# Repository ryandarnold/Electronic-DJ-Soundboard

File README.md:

# Electronic-DJ-Soundboard
The Electronic DJ Soundboard I designed in Eagle while serving as hardware lead on a 4-person team. I picked out the chips, designed the circuit, performed layout, soldered all components and tested and verified the board with a power supply and digital multimeter. 

I also coordinated with the embedded software lead on GPIO pin assignments, I/O functionality, communication protocol usage, and peripheral connections to support embedded firmware development.

<p align="center">
  
  <br>
  <em> The DJ circuit board outside its enclosure. I laser cut the enclosure and sanded it so it would fit together. </em>
</p>

<p align="center">
  
  <br>
  <em> The DJ circuit board from another angle. </em>
</p>

<p align="center">
  
  <br>
  <em> The main DJ circuit board.</em>
</p>

## Hardware: 

1. **TM4C123GH6PMI microcontroller launchpad** (as the main MCU for the project)
2. **Ceramic and Tantalum capacitors** (various purposes)
3. **ESP8266 Wifi module** (for saving user-made sound clips)
4. **TLV5618ACP DAC** (for outputting to the two speakers)
5. **MC34119 audio amplifier** (for amplifying the DAC output to the speakers)
6. **ULN2803a transistor array** (for powering the LED arrays)
7. **LM4041CILPR shunt voltage reference** (required for the TLV DAC)
8. **Resistors** (various purposes)
9. **Wire nuts** (for connecting the LEDs to the transistor array)
10. **LM2937 3.3 V regulator** (for powering different parts of the board)
11. **Testpoints** (for verifying that different parts of the board work)
12. **Blue, Red and Yellow LEDs** (to light the translucent buttons when pushed)
13. **MC7805ABTG 5V regulator** (for powering the LED array)
14. **8-ohm speakers** (for outputting user-made sounds)
15. **Audio jack** (so you can choose to use the built-in speakers or attach your own personal speaker for better sound quality)
16. **Pin headers**(to connect the launchpad to the board, and to have maximum flexibility in testing prototype)
17. **DC power connector** (to power the board)
18. **ST7735R LCD** (for displaying info to the user)
19. **Wood enclosure** (to store all electronics)
20. **Turn potentiometer** (for volume change)
21. **Slide potentiometer** (for tone change)

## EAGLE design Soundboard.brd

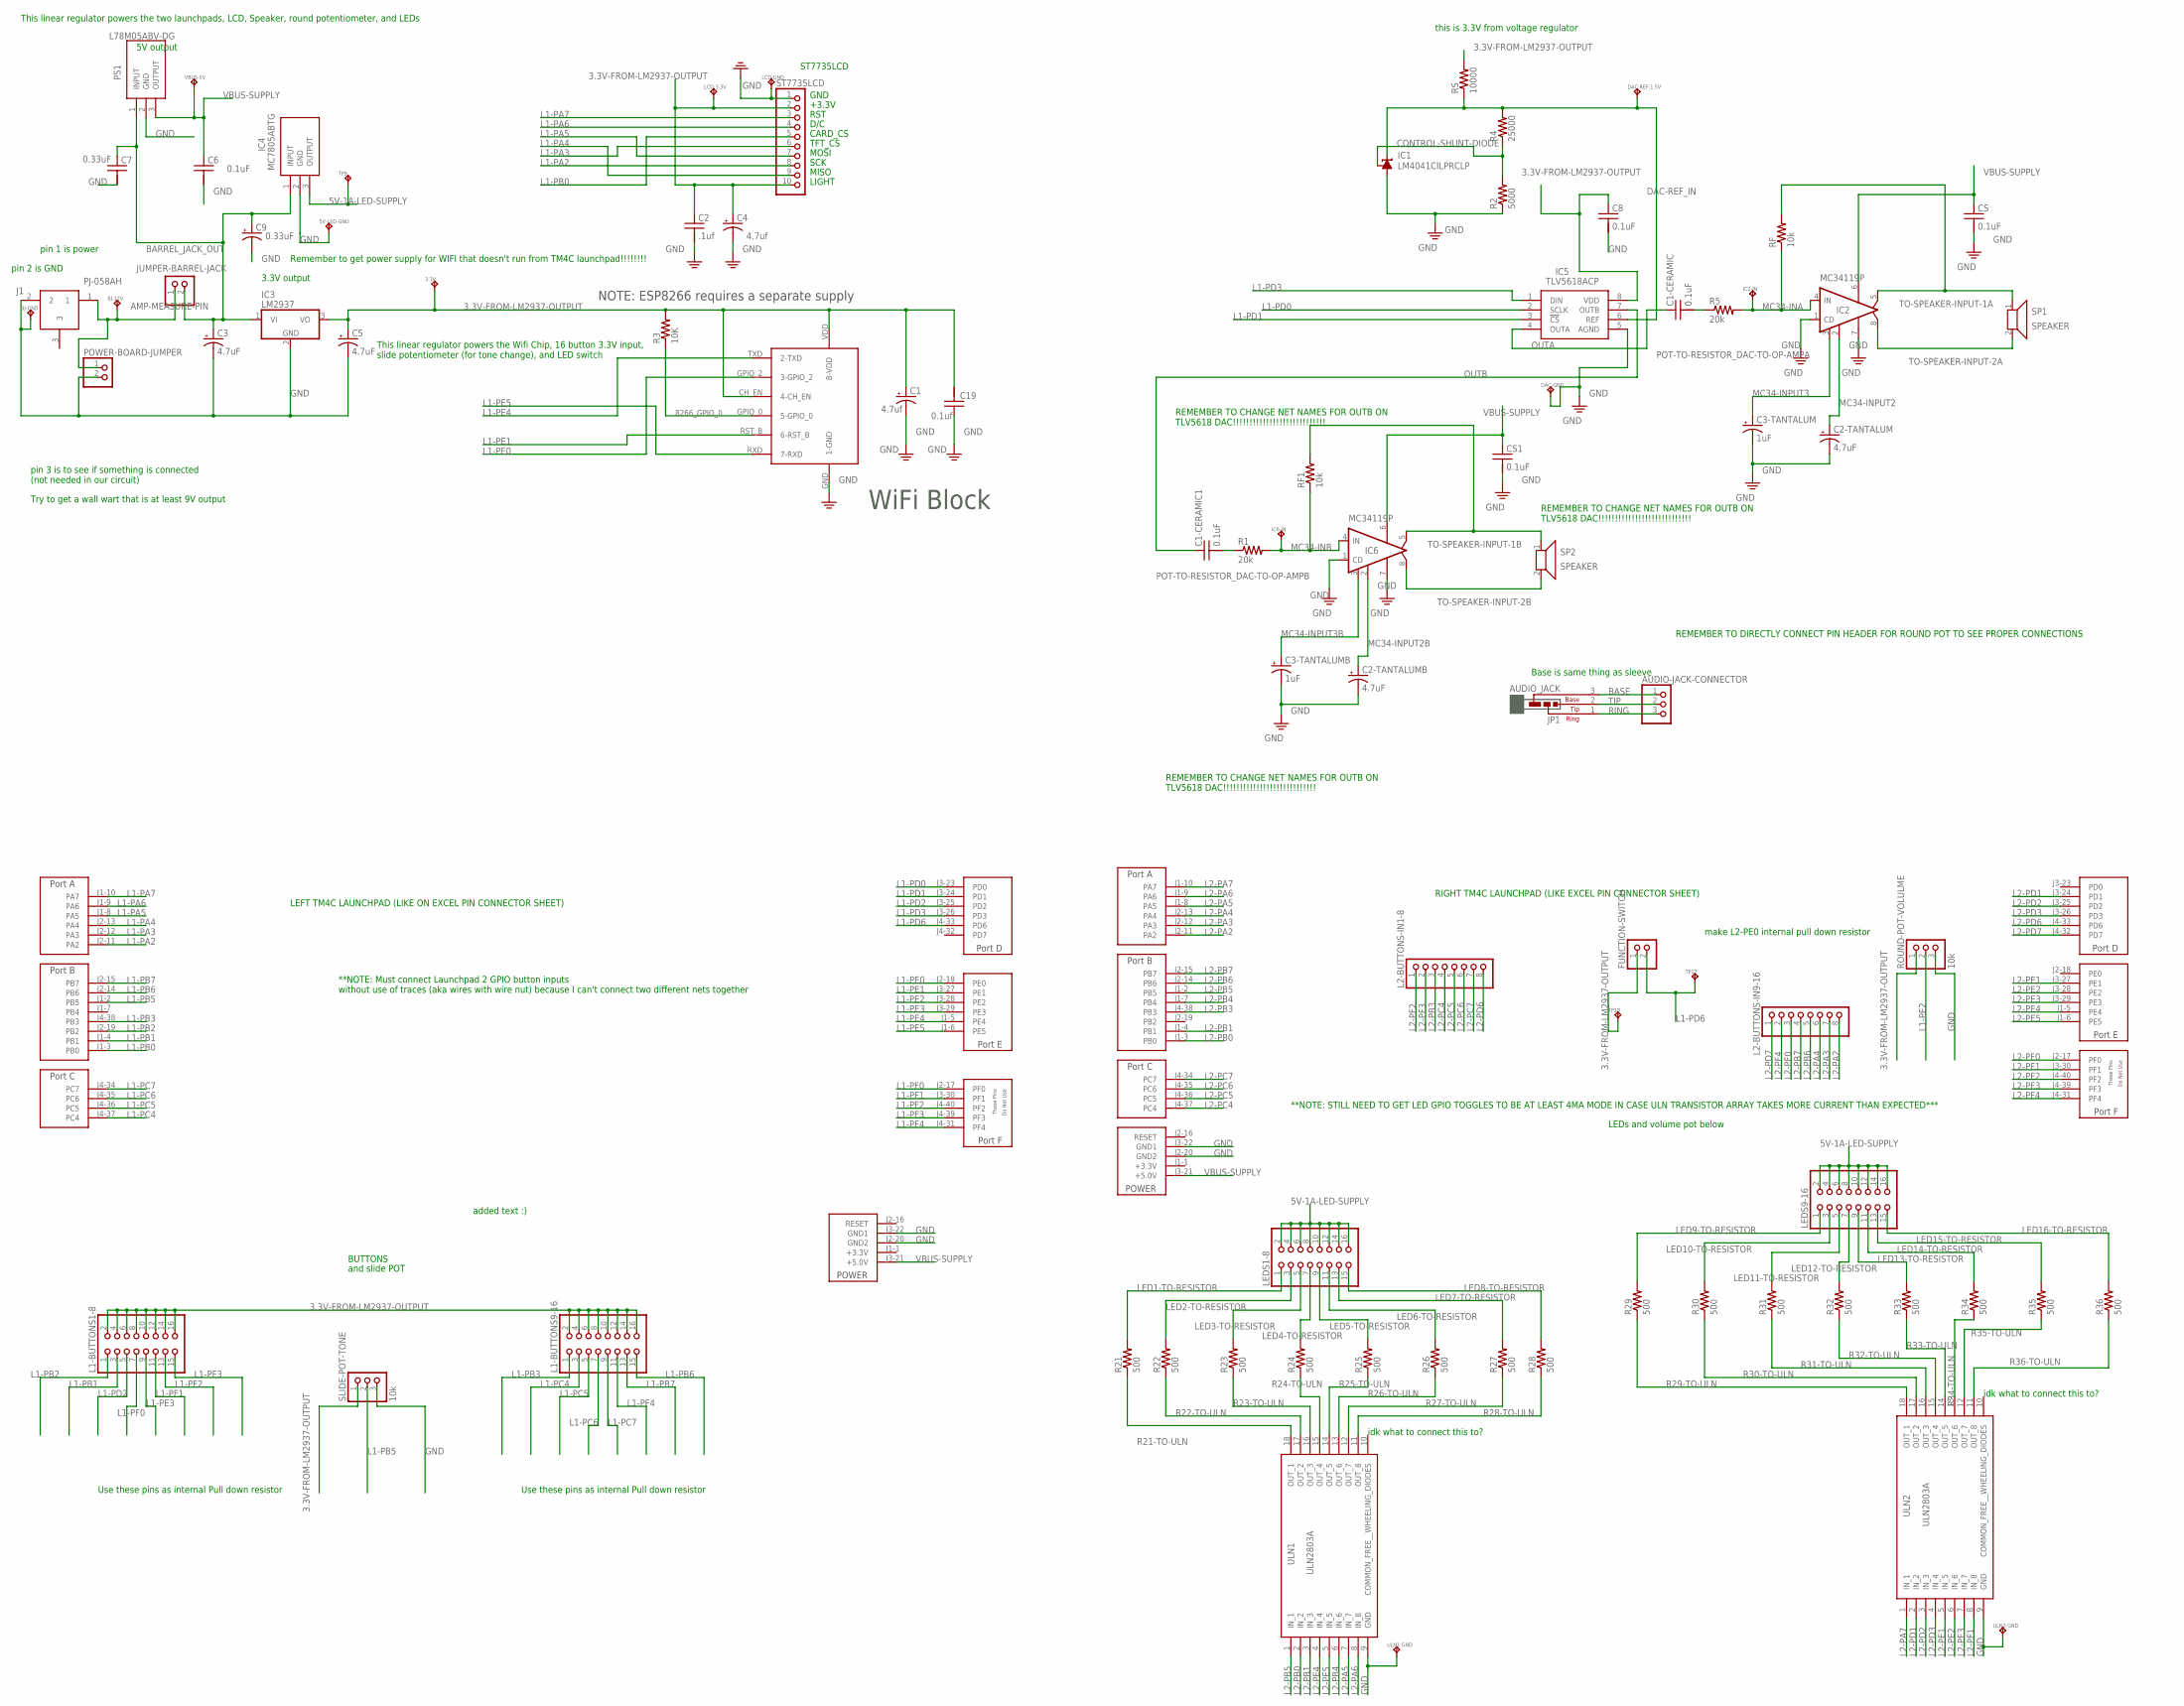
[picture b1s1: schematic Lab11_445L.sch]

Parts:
3.3V, 5V-LED-GND: TP_KEYSTONE500X; P1.1MM
AMP-MEASURE-PIN: PINHD-1X2; 1X02
AUDIO-JACK-CONNECTOR: PINHD-1X3; 1X03
BJ-12V: TP_KEYSTONE500X; P1.1MM
BJ-GND: TP_KEYSTONE500X; P1.1MM
C1, C4: 4.7uf; CAP200MILPOLARIZED
C1-CERAMIC, C1-CERAMIC1, C8: 0.1uF; CAP100MIL
C2: .1uf; CAP200MIL
C2-TANTALUM, C2-TANTALUMB, C3, C5: 4.7uF; CAP200MILPOLARIZED
C3-TANTALUM, C3-TANTALUMB: 1uF; CAP200MILPOLARIZED
C6: 0.1uF; CAP200MIL
C7: 0.33uF; CAP200MIL
C9: 0.33uF; CAP200MILPOLARIZED
C19: 0.1uf; CAP200MIL
CS, CS1: 0.1uF; CAP100MIL
DAC-GND: TP_KEYSTONE500X; P1.1MM
DAC-REF-1.5V: TP_KEYSTONE500X; P1.1MM
FUNCTION-SWITCH: PINHD-1X2; 1X02
IC1: LM4041CILPRCLP; LP_O-PBCY-W3
IC2, IC6: MC34119P; DIL08
IC2-IN, IC6-IN: TP_KEYSTONE500X; P1.1MM
IC3: LM2937; TO220
IC4: MC7805ABTG; TO254P482X997X2018-3P
IC5: TLV5618ACP; DIP794W53P254L959H508Q8N
J1: PJ-058AH; PJ058AH
JP1: AUDIO_JACK; JACK
L1-BUTTONS1-8, L1-BUTTONS9-16: PINHD-2X8; 2X08
L2-BUTTONS-IN1-8, L2-BUTTONS-IN9-16: PINHD-1X8; 1X08
LCD-3.3V: TP_KEYSTONE500X; P1.1MM
LCD-GND: TP_KEYSTONE500X; P1.1MM
LEDS1-8, LEDS9-16: PINHD-2X8; 2X08
POWER-BOARD-JUMPER: PINHD-1X2; 1X02
PS1: L78M05ABV-DG; TO255P460X1020X2008-3P
R1, R5: 20k; RES200MIL
R2: 5000; RES200MIL
R3: 10K; RES300MIL
R4: 25000; RES200MIL
R21, R22, R23, R24, R25, R26, R27, R28, R29, R30, R31, R32, R33, R34, R35, R36: 500; RES300MIL
RF, RF1: 10k; RES200MIL
ROUND-POT-VOLULME: 10k; 1X03
RS: 10000; RES200MIL
SLIDE-POT-TONE: 10k; 1X03
SP1, SP2: SPEAKER; 1X02
ST7735LCD: PINHD-1X10; 1X10
TP9, TP17, TP18: TP_KEYSTONE500X; P1.1MM
U$1: ESP_8266; ESP8266
U$2, U$3: TM4C_BP; TM4C_BOOSTER_PACK
ULN1, ULN2: ULN2803A; DIP850W46P254L2324H393Q18N
ULN1-GND, ULN2-GND: TP_KEYSTONE500X; P1.1MM
VBUS-5V: TP_KEYSTONE500X; P1.1MM

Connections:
3.3V-FROM-LM2937-OUTPUT: 3.3V.TP, C1.+, C2.1, C4.+, C5.+, C8.1, C19.2, FUNCTION-SWITCH.1, IC3.3 (VO), IC5.8 (VDD), L1-BUTTONS1-8.2, L1-BUTTONS1-8.4, L1-BUTTONS1-8.6, L1-BUTTONS1-8.8, L1-BUTTONS1-8.10, L1-BUTTONS1-8.12, L1-BUTTONS1-8.14, L1-BUTTONS1-8.16, L1-BUTTONS9-16.2, L1-BUTTONS9-16.4, L1-BUTTONS9-16.6, L1-BUTTONS9-16.8, L1-BUTTONS9-16.10, L1-BUTTONS9-16.12, L1-BUTTONS9-16.14, L1-BUTTONS9-16.16, LCD-3.3V.TP, R3.2, ROUND-POT-VOLULME.1, RS.2, SLIDE-POT-TONE.1, ST7735LCD.2, ST7735LCD.10, TP18.TP, U$1.CH_EN (4-CH_EN), U$1.VDD (8-VDD)
5V-1A-LED-SUPPLY: IC4.3 (OUTPUT), LEDS1-8.2, LEDS1-8.4, LEDS1-8.6, LEDS1-8.8, LEDS1-8.10, LEDS1-8.12, LEDS1-8.14, LEDS1-8.16, LEDS9-16.2, LEDS9-16.4, LEDS9-16.6, LEDS9-16.8, LEDS9-16.10, LEDS9-16.12, LEDS9-16.14, LEDS9-16.16, TP9.TP
8266_GPIO_0: R3.1, U$1.GPIO_0 (5-GPIO_0)
BARREL_JACK_OUT: AMP-MEASURE-PIN.1, BJ-12V.TP, J1.1, POWER-BOARD-JUMPER.1
BASE: AUDIO-JACK-CONNECTOR.1, JP1.3 (BASE)
CONTROL-SHUNT-DIODE: IC1.1 (FB), R2.2, R4.1
DAC-REF_IN: DAC-REF-1.5V.TP, IC1.2 (C), IC5.6 (REF), R4.2, RS.1
GND: 5V-LED-GND.TP, BJ-GND.TP, C1.-, C2.2, C2-TANTALUM.-, C2-TANTALUMB.-, C3.-, C3-TANTALUM.-, C3-TANTALUMB.-, C4.-, C5.-, C6.2, C7.2, C8.2, C9.-, C19.1, CS.2, CS1.2, DAC-GND.TP, IC1.3 (A), IC2.1 (CD), IC2.7 (GND), IC3.2 (GND), IC4.2 (GND), IC5.5 (AGND), IC6.1 (CD), IC6.7 (GND), J1.2, LCD-GND.TP, POWER-BOARD-JUMPER.2, PS1.2 (GND), R2.1, ROUND-POT-VOLULME.3, SLIDE-POT-TONE.3, ST7735LCD.1, U$1.GND (1-GND), U$2.J2-20 (GND2), U$2.J3-22 (GND1), U$3.J2-20 (GND2), U$3.J3-22 (GND1), ULN1.9 (GND), ULN1-GND.TP, ULN2.9 (GND), ULN2-GND.TP
JUMPER-BARREL-JACK: AMP-MEASURE-PIN.2, C3.+, C7.1, C9.+, IC3.1 (VI), IC4.1 (INPUT), PS1.1 (INPUT)
L1-PA2: ST7735LCD.8, U$2.J2-11 (PA2)
L1-PA3: ST7735LCD.6, U$2.J2-12 (PA3)
L1-PA4: ST7735LCD.9, U$2.J2-13 (PA4)
L1-PA5: ST7735LCD.7, U$2.J1-8 (PA5)
L1-PA6: ST7735LCD.4, U$2.J1-9 (PA6)
L1-PA7: ST7735LCD.3, U$2.J1-10 (PA7)
L1-PB0: ST7735LCD.5, U$2.J1-3 (PB0)
L1-PB1: L1-BUTTONS1-8.3, U$2.J1-4 (PB1)
L1-PB2: L1-BUTTONS1-8.1, U$2.J2-19 (PB2)
L1-PB3: L1-BUTTONS9-16.1, U$2.J4-38 (PB3)
L1-PB5: SLIDE-POT-TONE.2, U$2.J1-2 (PB5)
L1-PB6: L1-BUTTONS9-16.15, U$2.J2-14 (PB6)
L1-PB7: L1-BUTTONS9-16.13, U$2.J2-15 (PB7)
L1-PC4: L1-BUTTONS9-16.3, U$2.J4-37 (PC4)
L1-PC5: L1-BUTTONS9-16.5, U$2.J4-36 (PC5)
L1-PC6: L1-BUTTONS9-16.7, U$2.J4-35 (PC6)
L1-PC7: L1-BUTTONS9-16.9, U$2.J4-34 (PC7)
L1-PD0: IC5.2 (SCLK), U$2.J3-23 (PD0)
L1-PD1: IC5.3 (!CS), U$2.J3-24 (PD1)
L1-PD2: L1-BUTTONS1-8.5, U$2.J3-25 (PD2)
L1-PD3: IC5.1 (DIN), U$2.J3-26 (PD3)
L1-PD6: FUNCTION-SWITCH.2, TP17.TP, U$2.J4-33 (PD6)
L1-PE0: U$1.GPIO_2 (3-GPIO_2), U$2.J2-18 (PE0)
L1-PE1: U$1.RST_B (6-RST_B), U$2.J3-27 (PE1)
L1-PE2: ROUND-POT-VOLULME.2, U$2.J3-28 (PE2)
L1-PE3: L1-BUTTONS1-8.9, U$2.J3-29 (PE3)
L1-PE4: U$1.TXD (2-TXD), U$2.J1-5 (PE4)
L1-PE5: U$1.RXD (7-RXD), U$2.J1-6 (PE5)
L1-PF0: L1-BUTTONS1-8.7, U$2.J2-17 (PF0)
L1-PF1: L1-BUTTONS1-8.11, U$2.J3-30 (PF1)
L1-PF2: L1-BUTTONS1-8.13, U$2.J4-40 (PF2)
L1-PF3: L1-BUTTONS1-8.15, U$2.J4-39 (PF3)
L1-PF4: L1-BUTTONS9-16.11, U$2.J4-31 (PF4)
L2-PA2: L2-BUTTONS-IN9-16.8, U$3.J2-11 (PA2)
L2-PA3: L2-BUTTONS-IN9-16.7, U$3.J2-12 (PA3)
L2-PA4: L2-BUTTONS-IN9-16.6, U$3.J2-13 (PA4)
L2-PA5: U$3.J1-8 (PA5), ULN1.7 (IN_7)
L2-PA6: U$3.J1-9 (PA6), ULN1.8 (IN_8)
L2-PA7: U$3.J1-10 (PA7), ULN2.1 (IN_1)
L2-PB0: U$3.J1-3 (PB0), ULN1.2 (IN_2)
L2-PB1: U$3.J1-4 (PB1), ULN1.3 (IN_3)
L2-PB3: L2-BUTTONS-IN1-8.3, U$3.J4-38 (PB3)
L2-PB4: U$3.J1-7 (PB4), ULN1.6 (IN_6)
L2-PB5: U$3.J1-2 (PB5), ULN1.1 (IN_1)
L2-PB6: L2-BUTTONS-IN9-16.5, U$3.J2-14 (PB6)
L2-PB7: L2-BUTTONS-IN9-16.4, U$3.J2-15 (PB7)
L2-PC4: L2-BUTTONS-IN1-8.4, U$3.J4-37 (PC4)
L2-PC5: L2-BUTTONS-IN1-8.5, U$3.J4-36 (PC5)
L2-PC6: L2-BUTTONS-IN1-8.6, U$3.J4-35 (PC6)
L2-PC7: L2-BUTTONS-IN1-8.7, U$3.J4-34 (PC7)
L2-PD1: U$3.J3-24 (PD1), ULN2.2 (IN_2)
L2-PD2: U$3.J3-25 (PD2), ULN2.3 (IN_3)
L2-PD3: U$3.J3-26 (PD3), ULN2.4 (IN_4)
L2-PD6: L2-BUTTONS-IN1-8.8, U$3.J4-33 (PD6)
L2-PD7: L2-BUTTONS-IN9-16.1, U$3.J4-32 (PD7)
L2-PE1: U$3.J3-27 (PE1), ULN2.5 (IN_5)
L2-PE2: U$3.J3-28 (PE2), ULN2.6 (IN_6)
L2-PE3: U$3.J3-29 (PE3), ULN2.7 (IN_7)
L2-PE4: U$3.J1-5 (PE4), ULN1.4 (IN_4)
L2-PE5: U$3.J1-6 (PE5), ULN1.5 (IN_5)
L2-PF0: L2-BUTTONS-IN9-16.3, U$3.J2-17 (PF0)
L2-PF1: U$3.J3-30 (PF1), ULN2.8 (IN_8)
L2-PF2: L2-BUTTONS-IN1-8.1, U$3.J4-40 (PF2)
L2-PF3: L2-BUTTONS-IN1-8.2, U$3.J4-39 (PF3)
L2-PF4: L2-BUTTONS-IN9-16.2, U$3.J4-31 (PF4)
LED1-TO-RESISTOR: LEDS1-8.1, R21.2
LED2-TO-RESISTOR: LEDS1-8.3, R22.2
LED3-TO-RESISTOR: LEDS1-8.5, R23.2
LED4-TO-RESISTOR: LEDS1-8.7, R24.2
LED5-TO-RESISTOR: LEDS1-8.9, R25.2
LED6-TO-RESISTOR: LEDS1-8.11, R26.2
LED7-TO-RESISTOR: LEDS1-8.13, R27.2
LED8-TO-RESISTOR: LEDS1-8.15, R28.2
LED9-TO-RESISTOR: LEDS9-16.1, R29.2
LED10-TO-RESISTOR: LEDS9-16.3, R30.2
LED11-TO-RESISTOR: LEDS9-16.5, R31.2
LED12-TO-RESISTOR: LEDS9-16.7, R32.2
LED13-TO-RESISTOR: LEDS9-16.9, R33.2
LED14-TO-RESISTOR: LEDS9-16.11, R34.2
LED15-TO-RESISTOR: LEDS9-16.13, R35.2
LED16-TO-RESISTOR: LEDS9-16.15, R36.2
MC34-INA: IC2.4 (IN), IC2-IN.TP, R5.2, RF.1
MC34-INB: IC6.4 (IN), IC6-IN.TP, R1.2, RF1.1
MC34-INPUT2: C2-TANTALUM.+, IC2.2 (FC2)
MC34-INPUT2B: C2-TANTALUMB.+, IC6.2 (FC2)
MC34-INPUT3: C3-TANTALUM.+, IC2.3 (FC1)
MC34-INPUT3B: C3-TANTALUMB.+, IC6.3 (FC1)
OUTA: C1-CERAMIC.1, IC5.4 (OUTA)
OUTB: C1-CERAMIC1.1, IC5.7 (OUTB)
POT-TO-RESISTOR_DAC-TO-OP-AMPA: C1-CERAMIC.2, R5.1
POT-TO-RESISTOR_DAC-TO-OP-AMPB: C1-CERAMIC1.2, R1.1
R21-TO-ULN: R21.1, ULN1.18 (OUT_1)
R22-TO-ULN: R22.1, ULN1.17 (OUT_2)
R23-TO-ULN: R23.1, ULN1.16 (OUT_3)
R24-TO-ULN: R24.1, ULN1.15 (OUT_4)
R25-TO-ULN: R25.1, ULN1.14 (OUT_5)
R26-TO-ULN: R26.1, ULN1.13 (OUT_6)
R27-TO-ULN: R27.1, ULN1.12 (OUT_7)
R28-TO-ULN: R28.1, ULN1.11 (OUT_8)
R29-TO-ULN: R29.1, ULN2.18 (OUT_1)
R30-TO-ULN: R30.1, ULN2.17 (OUT_2)
R31-TO-ULN: R31.1, ULN2.16 (OUT_3)
R32-TO-ULN: R32.1, ULN2.15 (OUT_4)
R33-TO-ULN: R33.1, ULN2.14 (OUT_5)
R34-TO-ULN: R34.1, ULN2.13 (OUT_6)
R35-TO-ULN: R35.1, ULN2.12 (OUT_7)
R36-TO-ULN: R36.1, ULN2.11 (OUT_8)
RING: AUDIO-JACK-CONNECTOR.3, JP1.1 (RING)
TIP: AUDIO-JACK-CONNECTOR.2, JP1.2 (TIP)
TO-SPEAKER-INPUT-1A: IC2.5 (VO1), RF.2, SP1.1
TO-SPEAKER-INPUT-1B: IC6.5 (VO1), RF1.2, SP2.1
TO-SPEAKER-INPUT-2A: IC2.8 (VO2), SP1.2
TO-SPEAKER-INPUT-2B: IC6.8 (VO2), SP2.2
VBUS-SUPPLY: C6.1, CS.1, CS1.1, IC2.6 (VCC), IC6.6 (VCC), PS1.3 (OUTPUT), U$2.J3-21 (+5.0V), U$3.J3-21 (+5.0V), VBUS-5V.TP

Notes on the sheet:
WiFi Block
NOTE: ESP8266 requires a separate supply
Remember to get power supply for WIFI that doesn't run from TM4C launchpad!!!!!!!!
LEFT TM4C LAUNCHPAD (LIKE ON EXCEL PIN CONNECTOR SHEET)
RIGHT TM4C LAUNCHPAD (LIKE EXCEL PIN CONNECTOR SHEET)
Try to get a wall wart that is at least 9V output
5V output
3.3V output
This linear regulator powers the two launchpads, LCD, Speaker, round potentiometer, and LEDs
This linear regulator powers the Wifi Chip, 16 button 3.3V input, slide potentiometer (for tone change), and LED switch
BUTTONS
**NOTE: Must connect Launchpad 2 GPIO button inputs without use of traces (aka wires with wire nut) because I can't connect two different nets together
LEDs and volume pot below
and slide POT
pin 1 is power
pin 2 is GND
pin 3 is to see if something is connected (not needed in our circuit)
GND
+3.3V
RST
D/C
CARD_CS
TFT_CS
MOSI
SCK
MISO
LIGHT
ST7735LCD
REMEMBER TO DIRECTLY CONNECT PIN HEADER FOR ROUND POT TO SEE PROPER CONNECTIONS
Use these pins as internal Pull down resistor
REMEMBER TO CHANGE NET NAMES FOR OUTB ON TLV5618 DAC!!!!!!!!!!!!!!!!!!!!!!!!!!!!
this is 3.3V from voltage regulator
make L2-PE0 internal pull down resistor
Base is same thing as sleeve
**NOTE: STILL NEED TO GET LED GPIO TOGGLES TO BE AT LEAST 4MA MODE IN CASE ULN TRANSISTOR ARRAY TAKES MORE CURRENT THAN EXPECTED***
added text :)
idk what to connect this to?

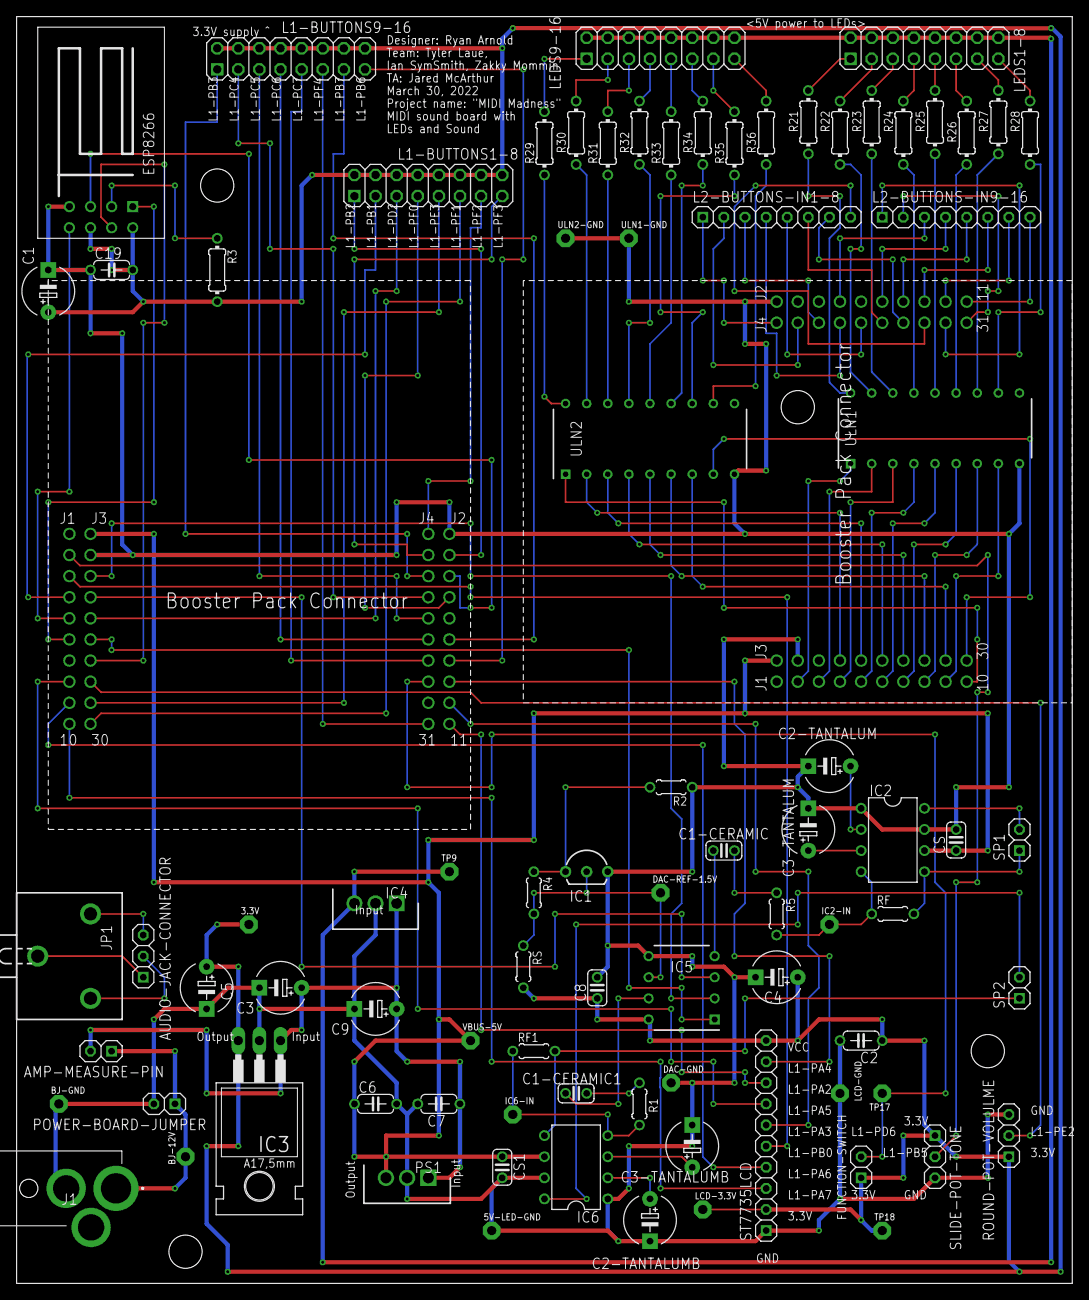
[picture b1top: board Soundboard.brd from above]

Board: 2 copper layers, 127.0 x 152.4 mm, 87 parts (0 on the bottom side), 123 nets.

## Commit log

2025-10-08 Update README with additional images and wording
    Added images to enhance the README documentation.
2025-10-08 Uploaded the main .sch and .brd files
2025-10-08 Changed name to Soundboard
2025-10-08 Added the Soundboard Schematic
2026-05-20 Revise project description in README.md
    Reword project description for clarity and conciseness.
2026-05-20 moved image around
    Removed duplicate image section and adjusted alignment.
2026-05-20 Update README with hardware specifications
    Added detailed hardware list for the project.
2026-05-20 Format microcontroller name in README
    Updated the formatting of the microcontroller name in the hardware section.
2026-05-20 Format hardware list with bold text
